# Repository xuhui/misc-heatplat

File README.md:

# misc-heatpalt
KiCAD PCB for a small heating pad

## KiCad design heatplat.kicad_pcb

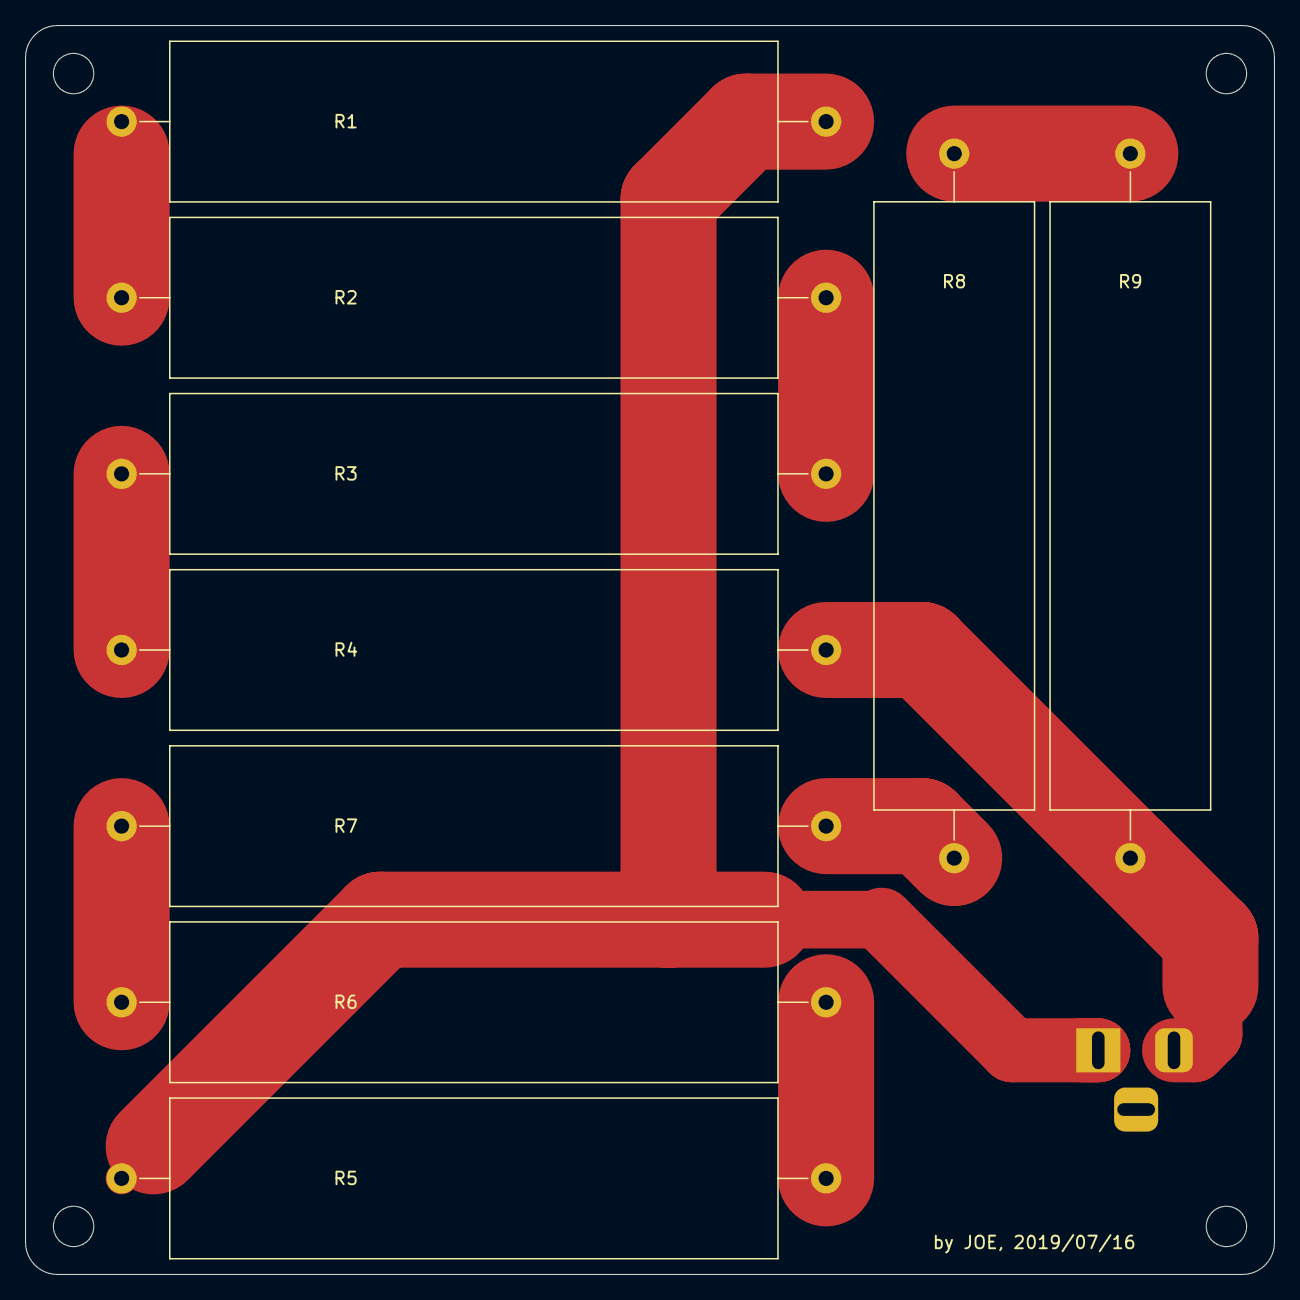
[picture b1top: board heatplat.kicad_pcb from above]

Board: 2 copper layers, 99.1 x 99.1 mm, 10 parts (1 on the bottom side), 9 nets.

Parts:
J1: Barrel_Jack_Switch; BarrelJack_Horizontal
R1, R2, R3, R4: 3R; R_Axial_Power_L48.0mm_W12.5mm_P55.88mm
R5, R6, R7: 2R2; R_Axial_Power_L48.0mm_W12.5mm_P55.88mm
R8, R9: 2R7; R_Axial_Power_L48.0mm_W12.5mm_P55.88mm

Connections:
unnamed: J1.1, R1.2, R5.2
unnamed: J1.2, R4.1, R9.1
unnamed: R1.1, R2.2
unnamed: R2.1, R3.2
unnamed: R3.1, R4.2
unnamed: R5.1, R6.2
unnamed: R6.1, R7.2
unnamed: R7.1, R8.2
unnamed: R8.1, R9.2

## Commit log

2019-07-16 init
2019-07-16 update resister values
